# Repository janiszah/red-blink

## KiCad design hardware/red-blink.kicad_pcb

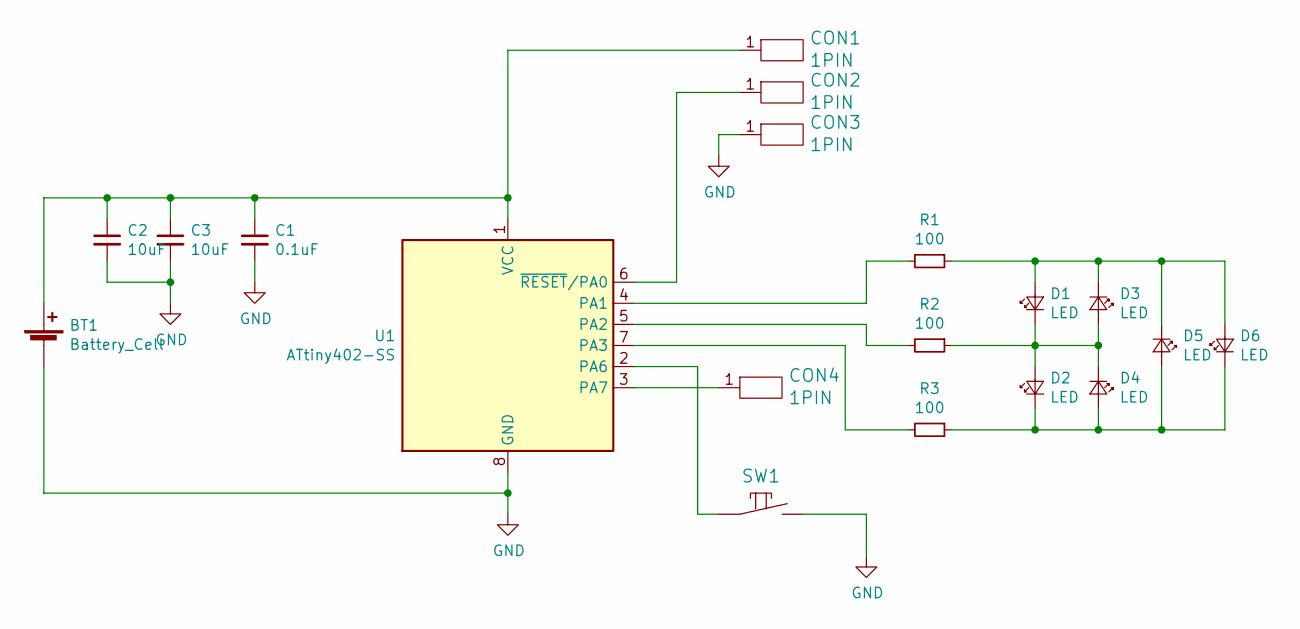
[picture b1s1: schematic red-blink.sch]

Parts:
BT1: Battery_Cell; BatteryHolder_Keystone_3002_1x2032
C1: 0.1uF; C_0805_2012Metric
C2, C3: 10uF; C_0805_2012Metric
CON1, CON2, CON3, CON4: 1PIN; TestPoint_2.00mm
D1, D2, D3, D4, D5, D6: LED; LED_3528
R1, R2, R3: 100; R_0805_2012Metric
SW1: SWT-2; SW_SPST_EVQQ2
U1: ATtiny402-SS; SOIC-8_3.9x4.9mm_P1.27mm

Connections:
GND: BT1.2 (-), C1.2, C2.2, C3.2, CON3.1, SW1.2, U1.8 (GND)
unnamed: BT1.1 (+), C1.1, C2.1, C3.1, CON1.1, U1.1 (VCC)
unnamed: CON2.1, U1.6 (~RESET~/PA0)
unnamed: CON4.1, U1.3 (PA7)
unnamed: D1.1 (K), D2.2 (A), D3.2 (A), D4.1 (K), R2.1
unnamed: D1.2 (A), D3.1 (K), D5.1 (K), D6.2 (A), R1.1
unnamed: D2.1 (K), D4.2 (A), D5.2 (A), D6.1 (K), R3.1
unnamed: R1.2, U1.4 (PA1)
unnamed: R2.2, U1.5 (PA2)
unnamed: R3.2, U1.7 (PA3)
unnamed: SW1.1, U1.2 (PA6)

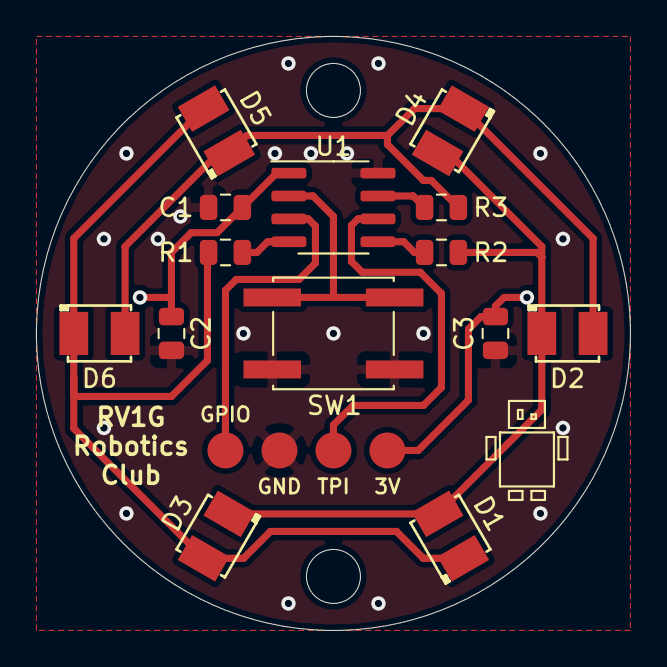
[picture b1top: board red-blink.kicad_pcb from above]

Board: 2 copper layers, 33.0 x 33.0 mm, 19 parts (1 on the bottom side), 11 nets.

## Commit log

2019-11-08 Working on PCB Layout
2019-12-04 Finished schematic and PCB
2019-12-18 Added Arduino sketch
2021-12-15 Improved power on/off. New 2 LED modes.
